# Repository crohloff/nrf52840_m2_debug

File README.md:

# nrf52840_m2_debug
Debug board for the M.2 module

## features
- access to all pins
- 4 buttons
- 4 LEDs
- USB-C connectivity
- TC2030 debug connector

## dimensions
- 60mm x 90mm

## board front

## board back

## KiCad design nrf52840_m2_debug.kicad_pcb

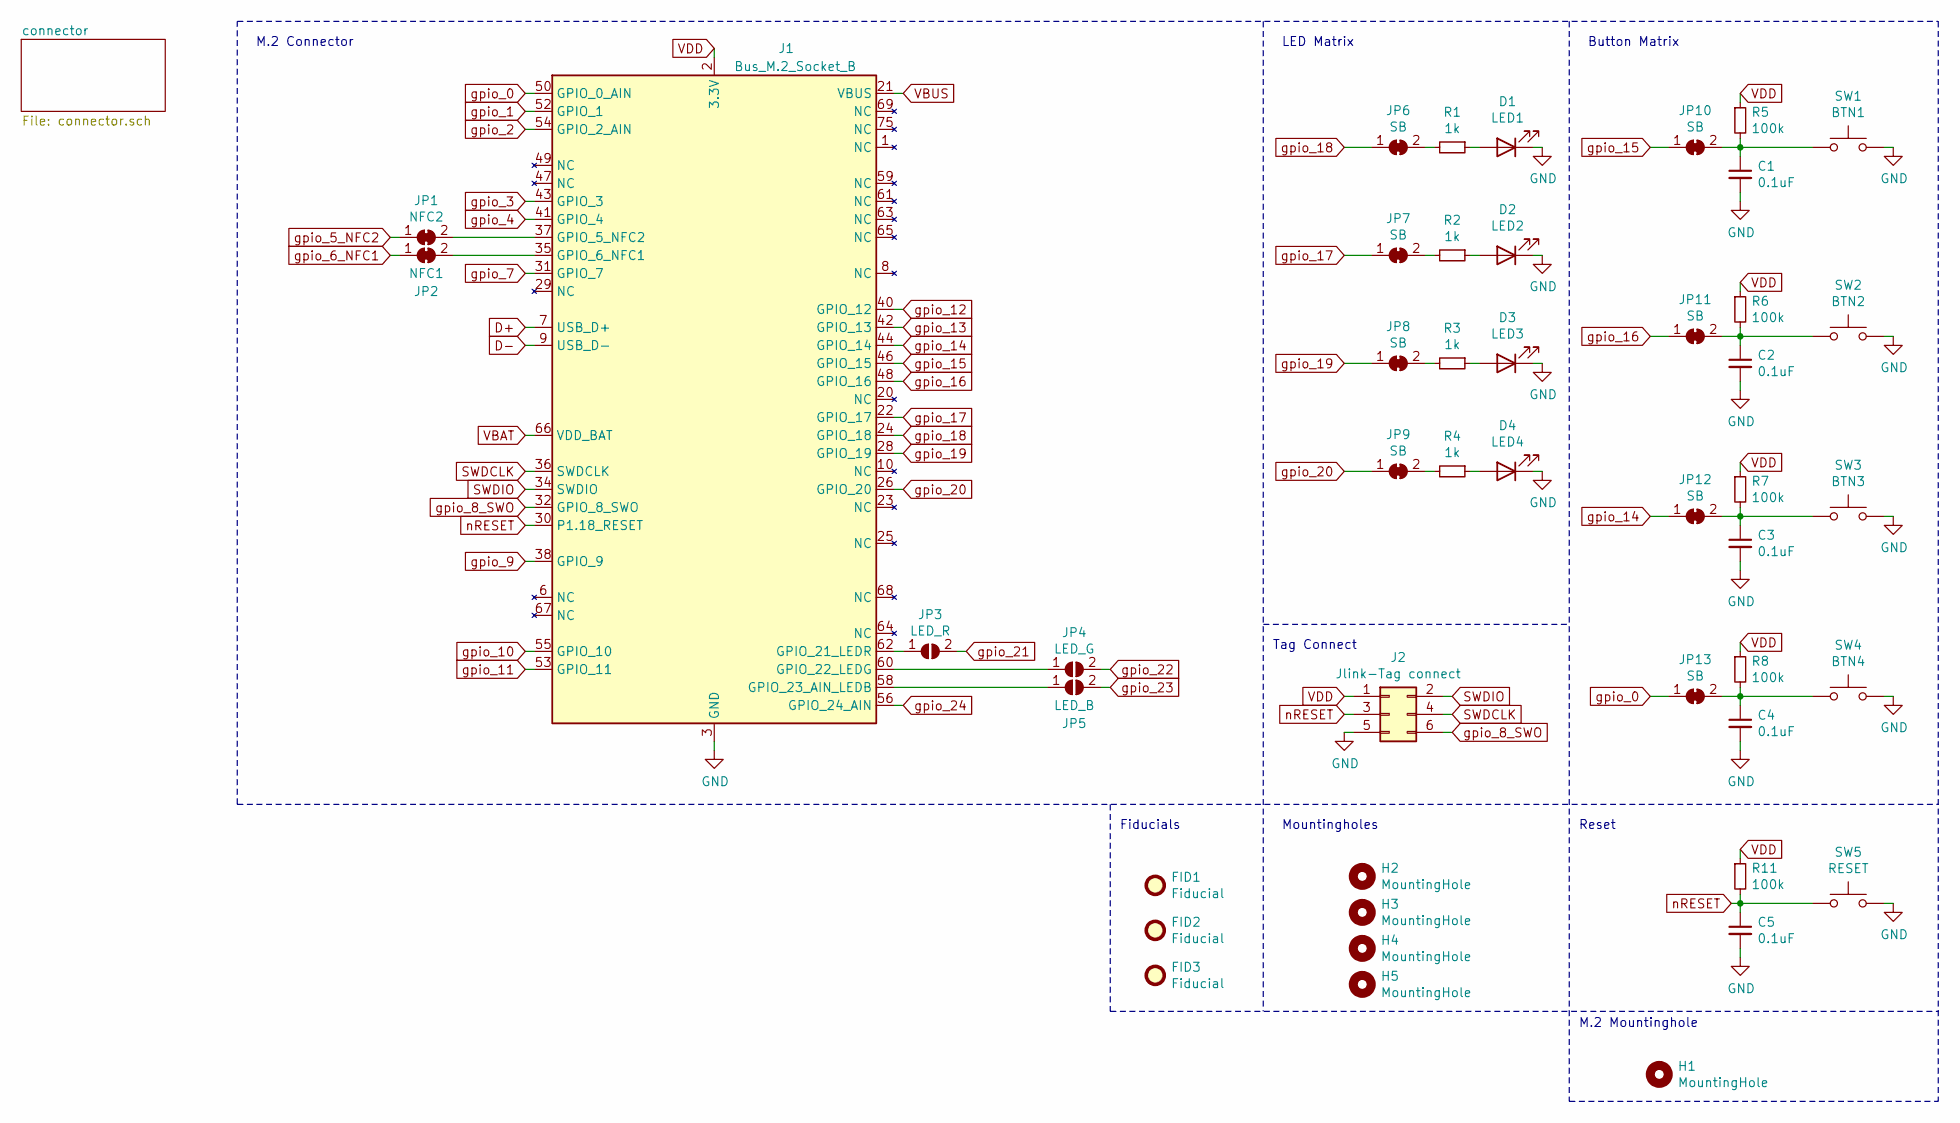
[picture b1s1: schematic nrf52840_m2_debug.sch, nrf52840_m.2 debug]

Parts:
C1, C2, C3, C4, C5: 0.1uF; C_0603_1608Metric; MFG P/N 063F104Z500CT; LCSC C83060
D1: LED1; LED_0603_1608Metric; MFG P/N LTST-C190KFKT; LCSC C157740
D2: LED2; LED_0603_1608Metric; MFG P/N LTST-C190KFKT; LCSC C157740
D3: LED3; LED_0603_1608Metric; MFG P/N LTST-C190KFKT; LCSC C157740
D4: LED4; LED_0603_1608Metric; MFG P/N LTST-C190KFKT; LCSC C157740
FID1, FID2, FID3: Fiducial; Fiducial_1mm_Mask2mm
H1, H2, H3, H4, H5: MountingHole; MountingHole_2.2mm_M2_Pad
J1: Bus_M.2_Socket_B; te_connectivity_121991190; MFG P/N 2199119; Mouser 571-1-2199119-0
J2: Jlink-Tag connect; Tag-Connect_TC2030-IDC-NL_2x03_P1.27mm_Vertical
JP1: NFC2; SolderJumper-2_P1.3mm_Bridged_RoundedPad1.0x1.5mm
JP2: NFC1; SolderJumper-2_P1.3mm_Bridged_RoundedPad1.0x1.5mm
JP3: LED_R; SolderJumper-2_P1.3mm_Open_RoundedPad1.0x1.5mm
JP4: LED_G; SolderJumper-2_P1.3mm_Open_RoundedPad1.0x1.5mm
JP5: LED_B; SolderJumper-2_P1.3mm_Open_RoundedPad1.0x1.5mm
JP6, JP7, JP8, JP9, JP10, JP11, JP12, JP13: SB; SolderJumper-2_P1.3mm_Bridged_RoundedPad1.0x1.5mm
R1, R2, R3, R4: 1k; R_0603_1608Metric; MFG P/N RC0603JR-071KL; LCSC C14676
R5, R6, R7, R8, R11: 100k; R_0603_1608Metric; MFG P/N RC0603JR-07100KL; LCSC C100048
SW1: BTN1; SW_SPST_PTS645; MFG P/N PTS645SH43SMTR92LFS; LCSC C285463
SW2: BTN2; SW_SPST_PTS645; MFG P/N PTS645SH43SMTR92LFS; LCSC C285463
SW3: BTN3; SW_SPST_PTS645; MFG P/N PTS645SH43SMTR92LFS; LCSC C285463
SW4: BTN4; SW_SPST_PTS645; MFG P/N PTS645SH43SMTR92LFS; LCSC C285463
SW5: RESET; SW_SPST_PTS645; MFG P/N PTS645SH43SMTR92LFS; LCSC C285463

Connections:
D+: J1.7 (USB_D+); also elsewhere on the board
D-: J1.9 (USB_D-); also elsewhere on the board
GND: C1.2, C2.2, C3.2, C4.2, C5.2, D1.1 (K), D2.1 (K), D3.1 (K), D4.1 (K), J1.3 (GND), J1.5 (GND), J1.11 (GND), J1.27 (GND), J1.33 (GND), J1.39 (GND), J1.45 (GND), J1.51 (GND), J1.57 (GND), J1.71 (GND), J1.73 (GND), J2.5, SW1.2, SW2.2, SW3.2, SW4.2, SW5.2; also elsewhere on the board
unnamed: C1.1, JP10.2 (B), R5.2, SW1.1
unnamed: C2.1, JP11.2 (B), R6.2, SW2.1
unnamed: C3.1, JP12.2 (B), R7.2, SW3.1
unnamed: C4.1, JP13.2 (B), R8.2, SW4.1
unnamed: D1.2 (A), R1.1
unnamed: D2.2 (A), R2.1
unnamed: D3.2 (A), R3.1
unnamed: D4.2 (A), R4.1
unnamed: J1.35 (GPIO_6_NFC1), JP2.2 (B)
unnamed: J1.37 (GPIO_5_NFC2), JP1.2 (B)
unnamed: J1.58 (GPIO_23_AIN_LEDB), JP5.1 (A)
unnamed: J1.60 (GPIO_22_LEDG), JP4.1 (A)
unnamed: J1.62 (GPIO_21_LEDR), JP3.1 (A)
unnamed: JP6.2 (B), R1.2
unnamed: JP7.2 (B), R2.2
unnamed: JP8.2 (B), R3.2
unnamed: JP9.2 (B), R4.2
SWDCLK: J1.36 (SWDCLK), J2.4; also elsewhere on the board
SWDIO: J1.34 (SWDIO), J2.2; also elsewhere on the board
VBAT: J1.66 (VDD_BAT); also elsewhere on the board
VBUS: J1.21 (VBUS); also elsewhere on the board
VDD: J1.2 (3.3V), J1.4 (3.3V), J1.70 (3.3V), J1.72 (3.3V), J1.74 (3.3V), J2.1, R5.1, R6.1, R7.1, R8.1, R11.1; also elsewhere on the board
gpio_0: J1.50 (GPIO_0_AIN), JP13.1 (A); also elsewhere on the board
gpio_1: J1.52 (GPIO_1); also elsewhere on the board
gpio_2: J1.54 (GPIO_2_AIN); also elsewhere on the board
gpio_3: J1.43 (GPIO_3); also elsewhere on the board
gpio_4: J1.41 (GPIO_4); also elsewhere on the board
gpio_5_NFC2: JP1.1 (A); also elsewhere on the board
gpio_6_NFC1: JP2.1 (A); also elsewhere on the board
gpio_7: J1.31 (GPIO_7); also elsewhere on the board
gpio_8_SWO: J1.32 (GPIO_8_SWO), J2.6; also elsewhere on the board
gpio_9: J1.38 (GPIO_9); also elsewhere on the board
gpio_10: J1.55 (GPIO_10); also elsewhere on the board
gpio_11: J1.53 (GPIO_11); also elsewhere on the board
gpio_12: J1.40 (GPIO_12); also elsewhere on the board
gpio_13: J1.42 (GPIO_13); also elsewhere on the board
gpio_14: J1.44 (GPIO_14), JP12.1 (A); also elsewhere on the board
gpio_15: J1.46 (GPIO_15), JP10.1 (A); also elsewhere on the board
gpio_16: J1.48 (GPIO_16), JP11.1 (A); also elsewhere on the board
gpio_17: J1.22 (GPIO_17), JP7.1 (A); also elsewhere on the board
gpio_18: J1.24 (GPIO_18), JP6.1 (A); also elsewhere on the board
gpio_19: J1.28 (GPIO_19), JP8.1 (A); also elsewhere on the board
gpio_20: J1.26 (GPIO_20), JP9.1 (A); also elsewhere on the board
gpio_21: JP3.2 (B); also elsewhere on the board
gpio_22: JP4.2 (B); also elsewhere on the board
gpio_23: JP5.2 (B); also elsewhere on the board
gpio_24: J1.56 (GPIO_24_AIN); also elsewhere on the board
nRESET: C5.1, J1.30 (P1.18_RESET), J2.3, R11.2, SW5.1; also elsewhere on the board

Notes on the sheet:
LED Matrix
Button Matrix
Reset
Mountingholes
M.2 Mountinghole
Tag Connect
M.2 Connector
Fiducials

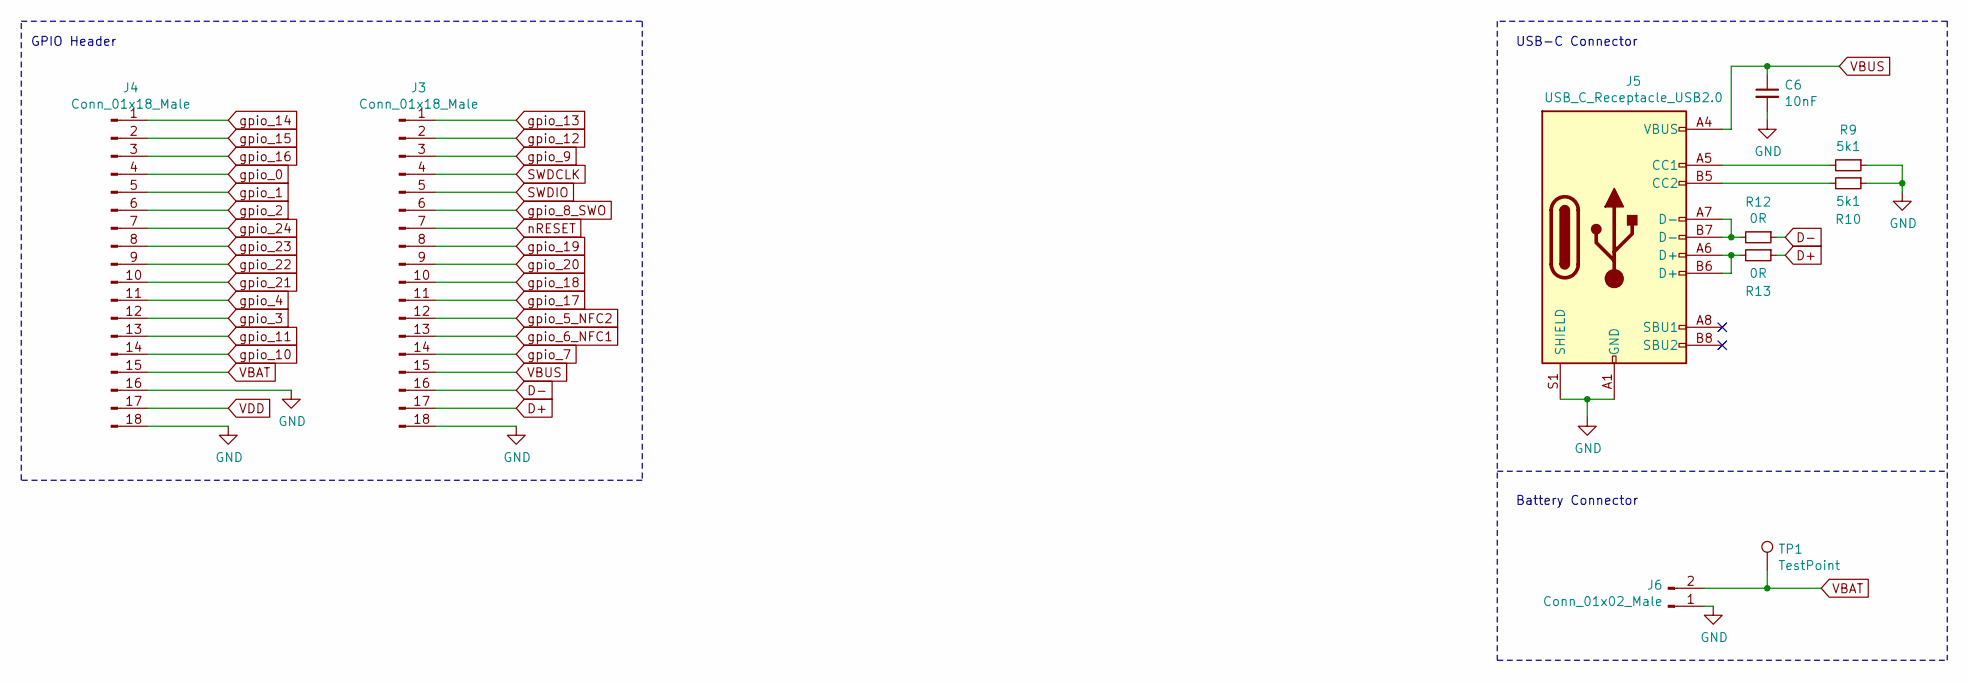
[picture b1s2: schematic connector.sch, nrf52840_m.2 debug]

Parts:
C6: 10nF; C_0603_1608Metric; MFG P/N CC0603KRX7R9BB103; LCSC C100042
J3, J4: Conn_01x18_Male; PinHeader_1x18_P2.54mm_Vertical; MFG P/N MTP125-1104S1; LCSC C358686
J5: USB_C_Receptacle_USB2.0; USB_C_Receptacle_XKB_U262-16XN-4BVC11; MFG P/N U262-161N-4BVC11; LCSC C319148
J6: Conn_01x02_Male; PinHeader_1x02_P2.54mm_Vertical; MFG P/N 210-91-02GB01; LCSC C390678
R9, R10: 5k1; R_0603_1608Metric; MFG P/N RC0603FR-075K11L; LCSC C112314
R12, R13: 0R; R_0603_1608Metric; MFG P/N RC0603JR-070RL; LCSC C95177
TP1: TestPoint; TestPoint_Pad_D1.0mm

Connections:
D+: J3.17, R13.1; also elsewhere on the board
D-: J3.16, R12.1; also elsewhere on the board
GND: C6.2, J3.18, J4.16, J4.18, J5.A1 (GND), J5.A12 (GND), J5.B1 (GND), J5.B12 (GND), J5.S1 (SHIELD), J6.1, R9.1, R10.1; also elsewhere on the board
unnamed: J5.A5 (CC1), R9.2
unnamed: J5.A6 (D+), J5.B6 (D+), R13.2
unnamed: J5.A7 (D-), J5.B7 (D-), R12.2
unnamed: J5.B5 (CC2), R10.2
SWDCLK: J3.4; also elsewhere on the board
SWDIO: J3.5; also elsewhere on the board
VBAT: J4.15, J6.2, TP1.1; also elsewhere on the board
VBUS: C6.1, J3.15, J5.A4 (VBUS), J5.A9 (VBUS), J5.B4 (VBUS), J5.B9 (VBUS); also elsewhere on the board
VDD: J4.17; also elsewhere on the board
gpio_0: J4.4; also elsewhere on the board
gpio_1: J4.5; also elsewhere on the board
gpio_2: J4.6; also elsewhere on the board
gpio_3: J4.12; also elsewhere on the board
gpio_4: J4.11; also elsewhere on the board
gpio_5_NFC2: J3.12; also elsewhere on the board
gpio_6_NFC1: J3.13; also elsewhere on the board
gpio_7: J3.14; also elsewhere on the board
gpio_8_SWO: J3.6; also elsewhere on the board
gpio_9: J3.3; also elsewhere on the board
gpio_10: J4.14; also elsewhere on the board
gpio_11: J4.13; also elsewhere on the board
gpio_12: J3.2; also elsewhere on the board
gpio_13: J3.1; also elsewhere on the board
gpio_14: J4.1; also elsewhere on the board
gpio_15: J4.2; also elsewhere on the board
gpio_16: J4.3; also elsewhere on the board
gpio_17: J3.11; also elsewhere on the board
gpio_18: J3.10; also elsewhere on the board
gpio_19: J3.8; also elsewhere on the board
gpio_20: J3.9; also elsewhere on the board
gpio_21: J4.10; also elsewhere on the board
gpio_22: J4.9; also elsewhere on the board
gpio_23: J4.8; also elsewhere on the board
gpio_24: J4.7; also elsewhere on the board
nRESET: J3.7; also elsewhere on the board

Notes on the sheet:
GPIO Header
USB-C Connector
Battery Connector

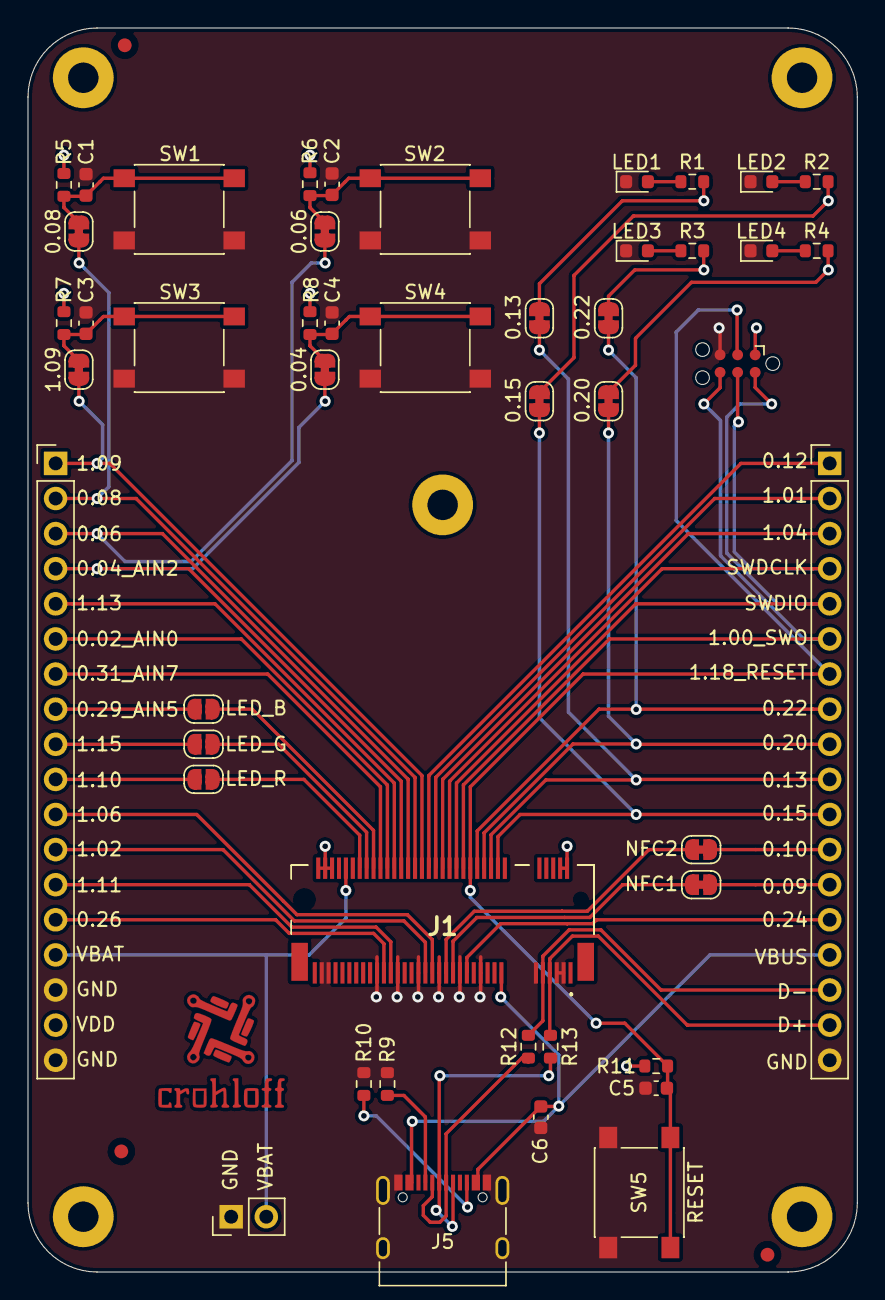
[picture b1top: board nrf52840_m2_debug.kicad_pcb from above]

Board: 2 copper layers, 60.0 x 90.0 mm, 56 parts (1 on the bottom side), 55 nets.

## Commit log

2021-05-13 update files
